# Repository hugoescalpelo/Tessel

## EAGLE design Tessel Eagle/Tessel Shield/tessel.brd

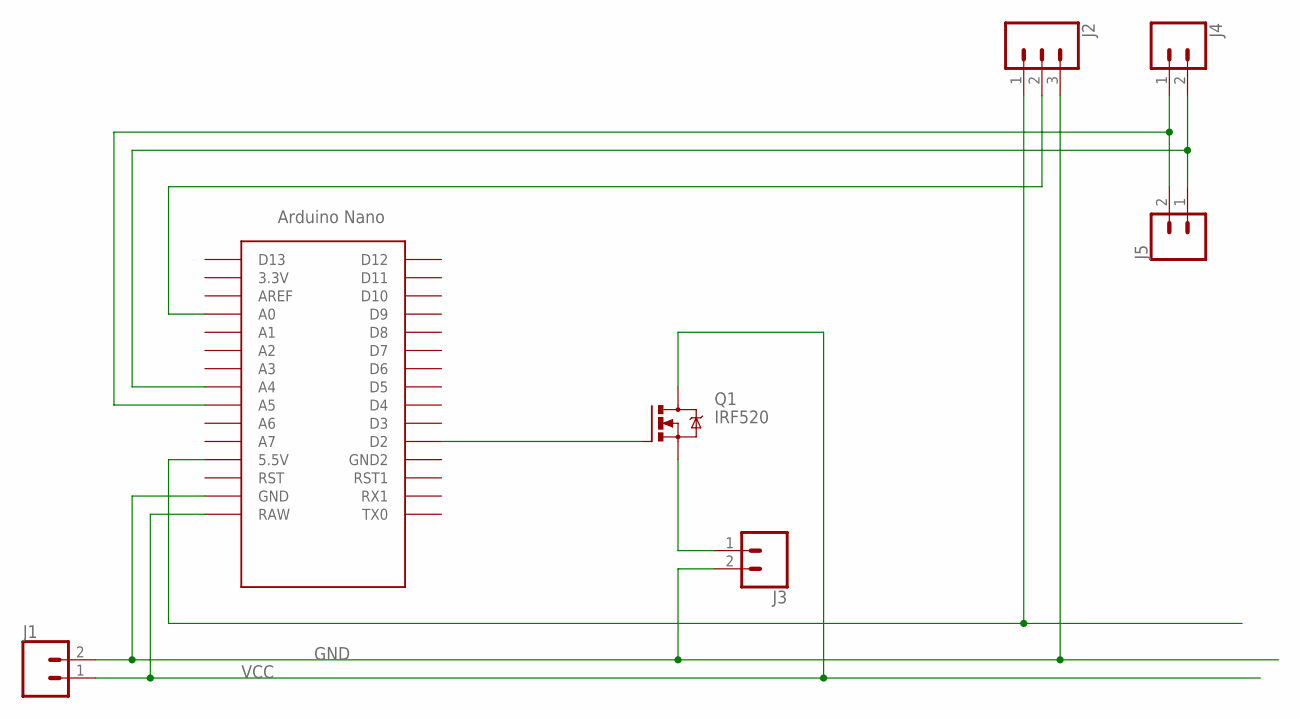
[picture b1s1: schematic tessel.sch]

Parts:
J1, J3, J4, J5: CONN_023.5MM_LOCK; SCREWTERMINAL-3.5MM-2_LOCK
J2: CONN_03LONGPADS; 1X03_LONGPADS
Q1: IRF520; TO220BV
U$1: NANO

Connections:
GND: J1.2, J2.3, J3.2, U$1.GND
unnamed: J2.1, U$1.5V (5.5V)
unnamed: Q1.G, U$1.D2
unnamed: J3.1, Q1.S
unnamed: J2.2, U$1.A0
unnamed: J4.1, J5.2, U$1.A5
unnamed: J4.2, J5.1, U$1.A4
VCC: J1.1, Q1.D, U$1.RAW

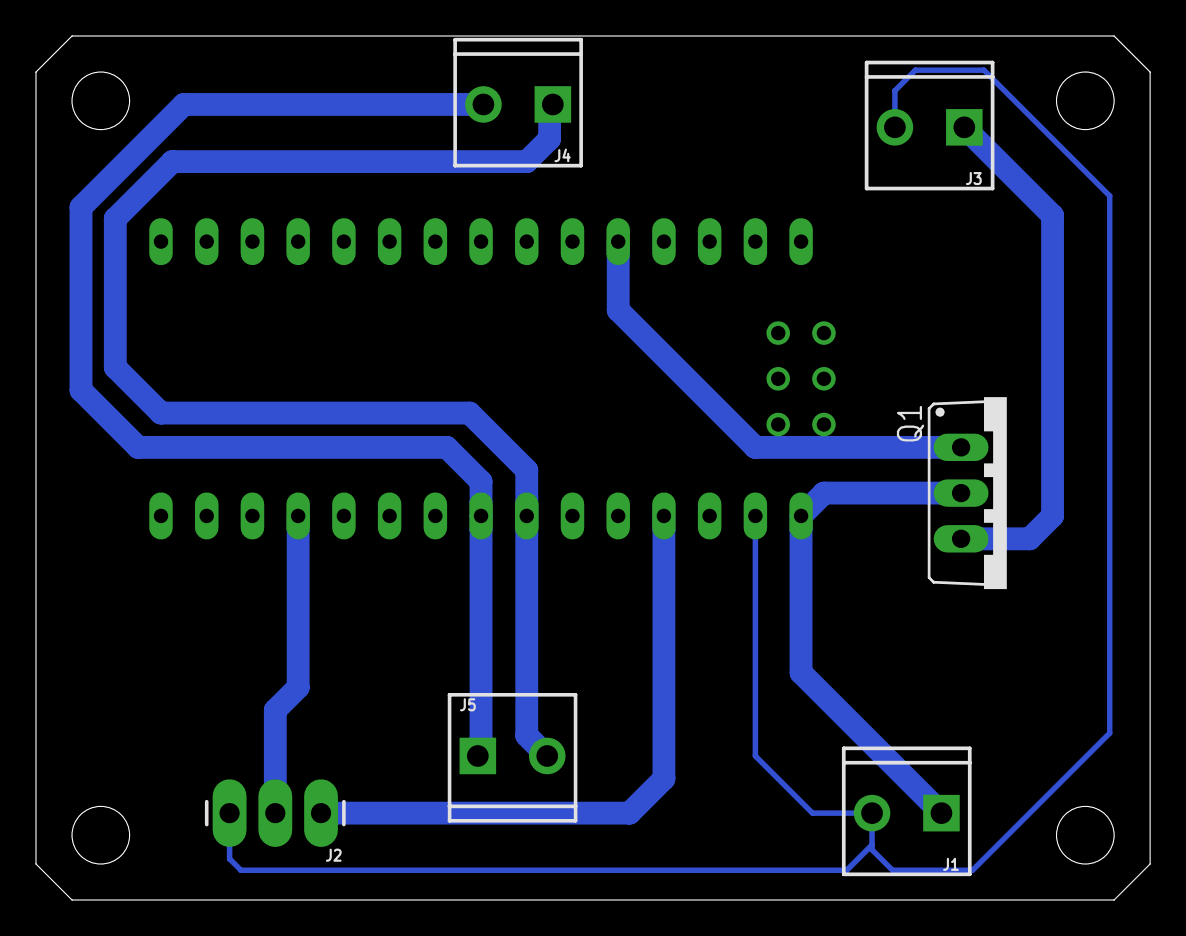
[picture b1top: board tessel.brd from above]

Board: 2 copper layers, 61.9 x 48.0 mm, 7 parts (0 on the bottom side), 8 nets.

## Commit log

2018-07-20 Shield for tessel project
2018-07-26 Circuit created

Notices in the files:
parts and their libraries:
SparkFun-Connectors: Licensing: Creative Commons ShareAlike 4.0 International - https://creativecommons.org/licenses/by-sa/4.0
